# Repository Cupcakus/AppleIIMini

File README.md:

# Apple IIe Mini powered by C.H.I.P
Here you will find everything you need to create your very own C.H.I.P. powered Apple IIe Mini computer.

# How it works
This Apple IIe mini is completely self contained and has a battery life of about 10 hours give or take.  I haven't actually tested it, so I'm guessing based on the stated life of the battery and the amount of currrent draw observed during testing.

The C.H.I.P. can use 3.3V to 5V power, however the LCD TFT screen requires 6V to 12V.  I solved this by using a 12V drone/RC battery and passed it through a cheap 5V buck converter to power the C.H.I.P.  I created a very simple PCB to accomplish this.  You do not need the PCB to complete this build, I created one just to keep things a bit tidy.

You can of course use a super cheap linear regular like an LM317 to do the same job, but the $5 buck converter is much more efficient and will extend the battery life.

A stock C.H.I.P is all you need, I could not get the emulator to run in headless mode, so you will need the standard firmware and then configure the emulator to auto run in the KDE desktop.

# Tools Required
- Soldering Iron
- Edge cutters (To cut off excess pins after soldering)
- Good 60/40 Solder
- 22 Guage or similar stranded hook up wire

# Electrical Components Required
If you are building it the exact same way I did, including the PCB this is what you will need
- 4x JS 2.0 PH Connectors Male & Female (For 12V In, 12V Out, Speaker Out, and Power Switch)
- 2x 40 Pin DIP headers
- 1x 4 pin 12v to 5v buck converter (Search EBay)
- 1x Small speaker (Digikey SP-1504 is what I used)
- 1x Lumineer 1300mAh 12V battery
- 1x Set of XT60 Drone battery connectors
- 1x 3S LiPo battery charger (Optional, but I'm sure you will want to charge the battery at some point)
- 1x 3.5" TFT LCD TV from Adafruit (https://www.adafruit.com/products/913)
- 1x Pushbutton toggle switch for power (https://www.adafruit.com/product/1683)

# 3D Prints
I used the excellent 3D models from Thingiverse of a user named option8 and printed them on my Zortrax M200 pinter at 0.19mm/Medium infill.  The original models are meant for a Raspberry Pi powered via USB, so I modified the base a bit for this self contained model.
- Apple II Enclosure (https://www.thingiverse.com/thing:340677)
- Apple II Monitor (http://www.thingiverse.com/thing:377253)
- Apple II Enclosed Base (http://www.thingiverse.com/thing:2103158)

I drilled a hole through the top of the enclosure into the monitor to run the wires for the monitor power, power switch, and video signals into the monitor.

Standard super glue seemed to work fine for gluing everything together.

# Paint
I followed option8's directions for painting with the following spray paints
- Montana GOLD (Sahara Yellow) for case
- Krylon Espresso for Keyboard/Accessories

# Video Signal
Unfortunately the composite video signal from the C.H.I.P. is not exposed on the pin headers, so I was forced to hack it in.  If you are able to find a small enough right angle 3.5mm to RCA video cable that works go for it.  I was not.

To hack in the video signal, simply attach a wire from the video signal on the C.H.I.P. PCB.  I have highlighted the correct pin here: [Video Pin](./BuildImages/VideoPin.png)

Connect the video GND to any available ground, I soldered it directly to the top of the 3.5mm connector on the C.H.I.P.

# Emulator
I am using a slightly modified version of LinApple-Pie which you can get here https://github.com/Cupcakus/linapple-pie

I have modified the original emulator a bit to make the menus more readable on the 320x240 screen.

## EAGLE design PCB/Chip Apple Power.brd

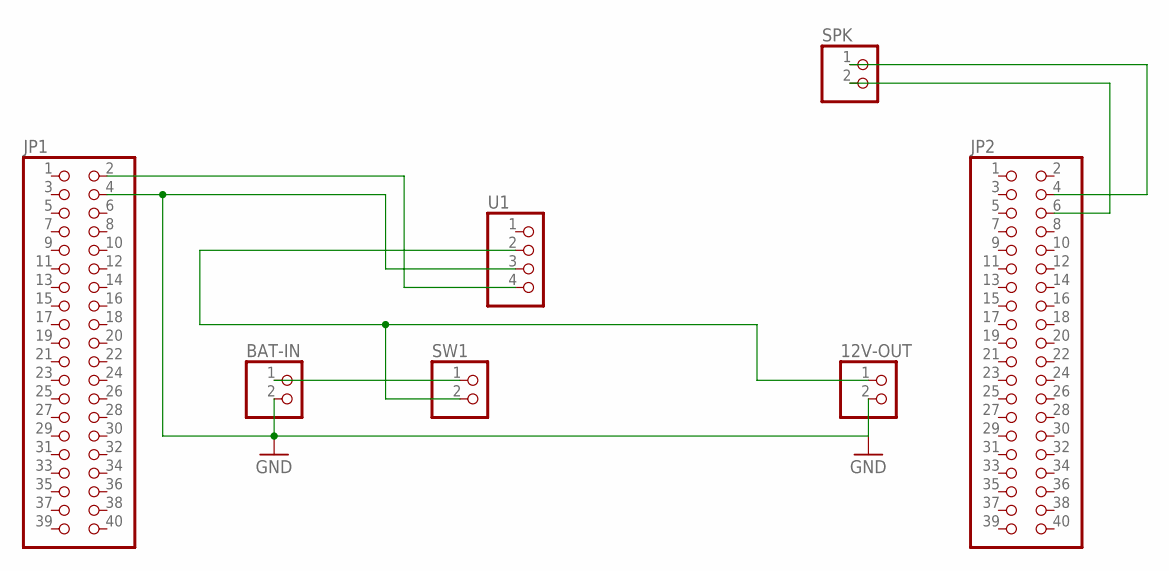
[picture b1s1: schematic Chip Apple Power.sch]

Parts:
12V-OUT: PINHD-1X2; 1X02
BAT-IN: PINHD-1X2; 1X02
JP1, JP2: PINHD-2X20; 2X20
SPK: PINHD-1X2; 1X02
SW1: PINHD-1X2; 1X02
U1: PINHD-1X4/90; 1X04/90

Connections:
GND: 12V-OUT.2, BAT-IN.2, JP1.4, U1.3
unnamed: BAT-IN.1, SW1.1
unnamed: 12V-OUT.1, SW1.2, U1.2
unnamed: JP2.4, SPK.1
unnamed: JP2.6, SPK.2
U1: JP1.2, U1.4

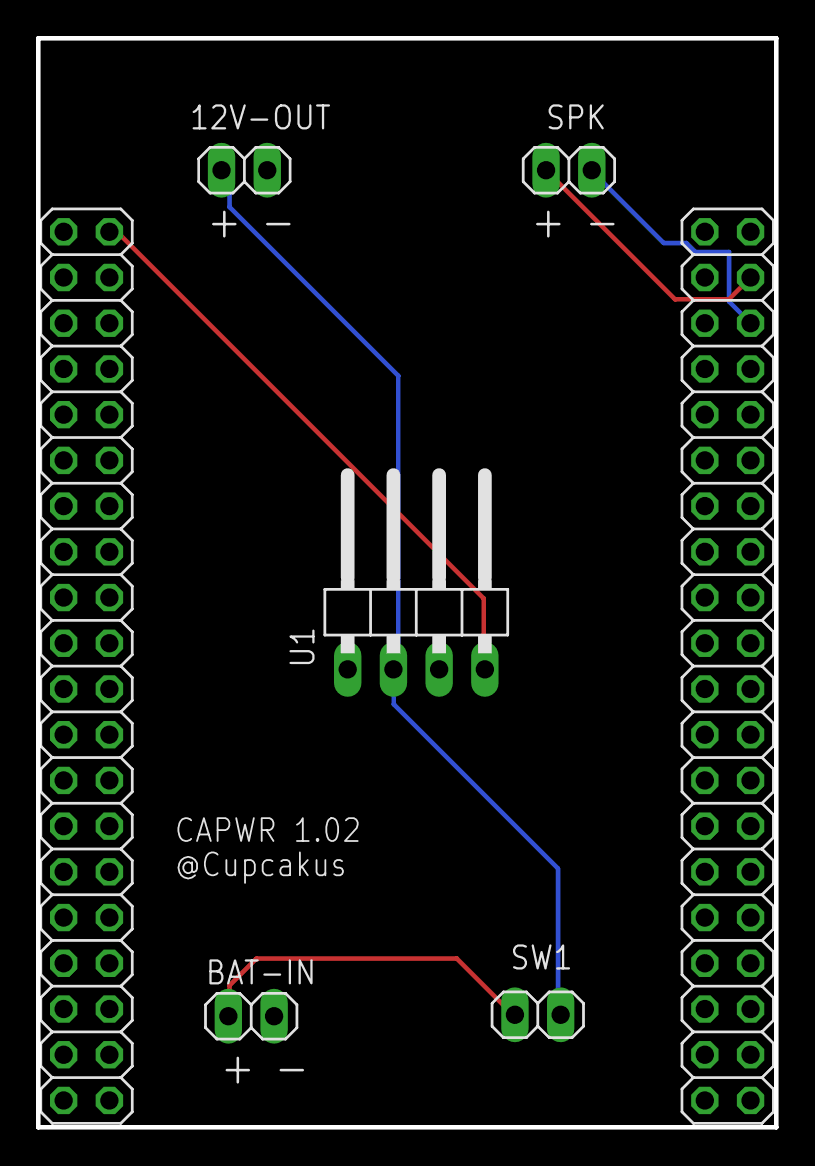
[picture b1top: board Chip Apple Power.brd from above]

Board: 2 copper layers, 41.0 x 60.5 mm, 7 parts (0 on the bottom side), 6 nets.

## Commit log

2017-02-11 Create Images
2017-02-11 Create temp
